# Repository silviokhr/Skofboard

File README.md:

# Split Ergonomic Wireless Gasket-Mounted Keyboard

<div align="center">
  
</div>

## Features

- **Ergonomic split design** — reduces wrist strain and promotes a more neutral typing position
- **Ortholinear layout**     — aligns keys in a grid, reducing finger travel distance with 3 dedicated thumb buttons
- **Gasket-mounted PCB**     — provides a dampened sound profile and soft keystroke feel
- **Magnetic closure**       — enables quick assembly and disassembly without tools
- **Reversible PCB design**  — single PCB works for both left and right halves
- **Hot-swappable switches** — easily swap or customize switches without soldering
- **ZMK firmware support**   — fully customizable keymap via ZMK Studio
- **Wireless connectivity**  — powered by the nice!nano v2.0 microcontroller

---

## Case

All case parts are CNC machined, and material selection significantly impacts the sound profile. The rigid aluminum base dampens resonance while the polycarbonate top provides acoustic transparency, and rounded internal surfaces minimize harsh reflections for a refined keystroke sound. STL files are included for 3D-printed case variants.

| Part | Material | Surface Finish |
|------|----------|----------------|
| Top casing | Polycarbonate (PC) | Blue-tinted vapor polishing |
| Bottom casing | Aluminum 6061 | Bead blasting + anodizing |

---

## Parts List (Bill of Materials)

Quantities are **per half** — a complete keyboard requires two of everything below.

| Qty | Component | Specification |
|-----|-----------|---------------|
| 8 | Corner magnet | Neodymium disc, ⌀4 × 3 mm |
| 16 | Edge magnet | Neodymium disc, ⌀2 × 3 mm |
| 6 | Large gasket foam | Poron, 4.5 × 7 × 2 mm |
| 2 | Small gasket foam | Poron, 4.5 × 4 × 2 mm |
| 4 | Rubber foot | ⌀8 × 1.6 mm |
| 1 | Microcontroller | nice!nano v2.0 |
| 2 | Microcontroller socket 12-pin | Mill Max 315-43-112-41-003000 |
| 24 | Socket pins | Mill Max 3320-0-00-15-00-00-03-0 |
| 1 | Battery | 3.7 V LiPo, 250 mAh, model 502030, 2P-PH connector |
| 1 | Battery connector | S2B-PH-K-S(LF)(SN) |
| 1 | Power switch | MSK12C02 (SMD slide switch) |
| 30 | Keyswitch | MX-format (any compatible switch) |
| 30 | Hotswap socket | Kailh MX-format |
| 30 | Diode | 1N4148W, SOD-123 |

### Part Notes

Only the parts below have constraints or behavior worth calling out; everything else fits as listed.

- **Magnets** — Cutouts are intentionally oversized to ensure a proper fit during assembly. Corner cutouts are ⌀4.1 mm × 3 mm deep; edge cutouts are ⌀2.1 mm × 3 mm deep.
- **Rubber feet** — Seat into ⌀8 mm × 1.5 mm-deep cutouts and must protrude a minimum of 0.1 mm below the case bottom for optimal grip.
- **Battery** — The cutout on the top plate is shared with the battery connector jack, which limits usable space. Optimal dimensions are **50 mm (H) × 20 mm (W) × 30 mm (D)**. ⚠️ Taller batteries are possible, but wider or longer batteries are not recommended and may not fit reliably.

---

## PCB Specifications

- **Layer count:** 2-layer
- **Material:** FR-4, 1.6 mm thickness
- **Copper weight:** 1 oz
- **Surface finish:** LeadFree HASL

**Design note:** The PCB switchplate (`SkofTopPlate.kicad_pcb`) is 1.6 mm FR-4 (standard manufacturing thickness), while standard MX switches are designed for 1.5 mm plates. Because of this 0.1 mm difference, switches fit securely but may feel slightly tight.

---

## Keymap

The default keymap is currently a placeholder and varies by region. To customize it, press the **`studio_unlock`** key on the left half — at **column 1, row 2** — to enter configuration mode in ZMK Studio.

---

## Assembly Guide

> Build is **per half** — repeat all steps for both. The PCB is reversible, so each half is configured by solder jumpers (step 3) before anything is populated.

**Case prep**

1. **Attach the feet** to the bottom casing.
2. **Glue in the magnets** (corner and edge) into their cutouts. ⚠️ Check polarity *before* gluing — all magnets must be oriented so the top and bottom casings attract when closed. (See Part Notes for fit.)

**PCB**

3. **Set the handedness** — close the solder-jumper bridges that configure the PCB for the left or right half (per the build files), **before** soldering any sockets:
   - **Microcontroller** jumpers — front (top) side
   - **Battery** jumpers — back (bottom) side
4. **Populate the PCB** — on the **back**, solder the diodes and hotswap sockets; on the **front**, solder the power switch, battery connector, and microcontroller sockets.
5. **Mount the nice!nano v2.0** — seat the header pins in the sockets, then mount the controller **face-down (component side against the PCB, bare back facing up)** and solder the pins so it stays removable.

**Power test** *(before switches — easier to fix solder issues now)*

6. **Connect the battery** with the power switch **off**, checking polarity.
7. **Flash and test** — flash the firmware (double-tap reset for the bootloader), power on, and confirm the half boots, pairs with the other half, and connects to your host.

**Plate + switches**

8. **Add the gasket foam** — place the foam strips in their positions per the build files.
9. **Install switches** — straighten any bent pins, fit 3–4 corner switches first to align the plate, then drop in the rest through the switchplate.

**Finish**

10. **Final check** — verify every key registers.
11. **Close the case** — join the top and bottom casings via the magnetic closure.

---

## Credits

This project uses open-source hardware footprints licensed under MIT and CC-BY-NC-SA 4.0 by Marco Massarelli (@ceoloide) and contributors.

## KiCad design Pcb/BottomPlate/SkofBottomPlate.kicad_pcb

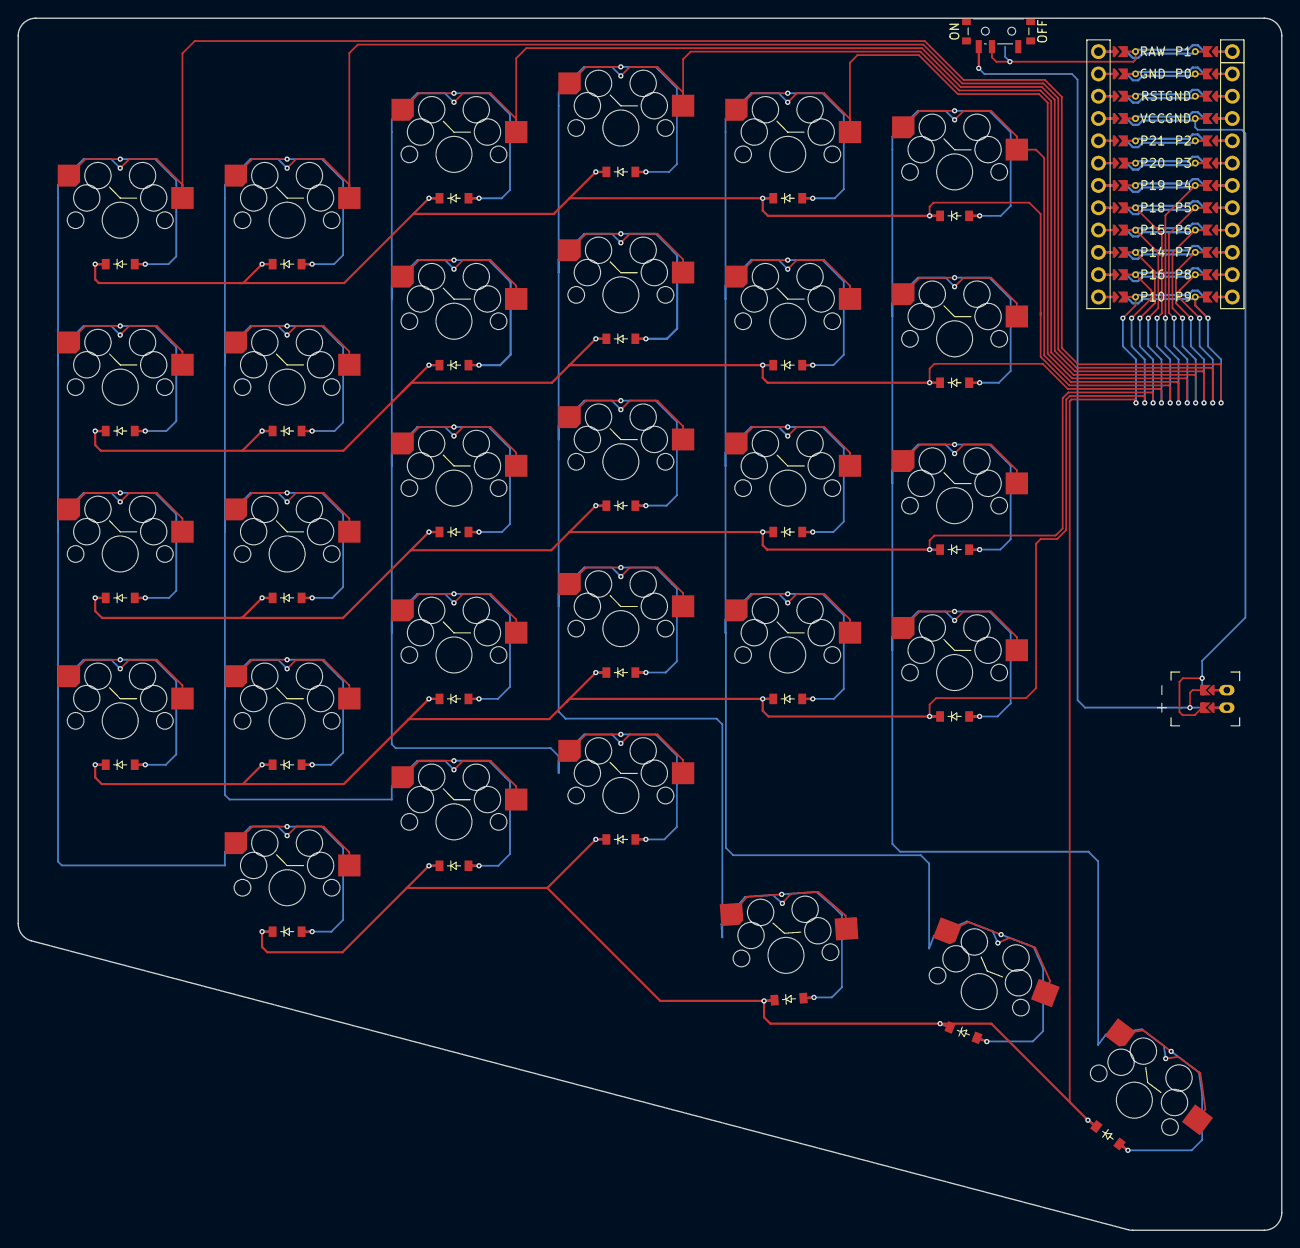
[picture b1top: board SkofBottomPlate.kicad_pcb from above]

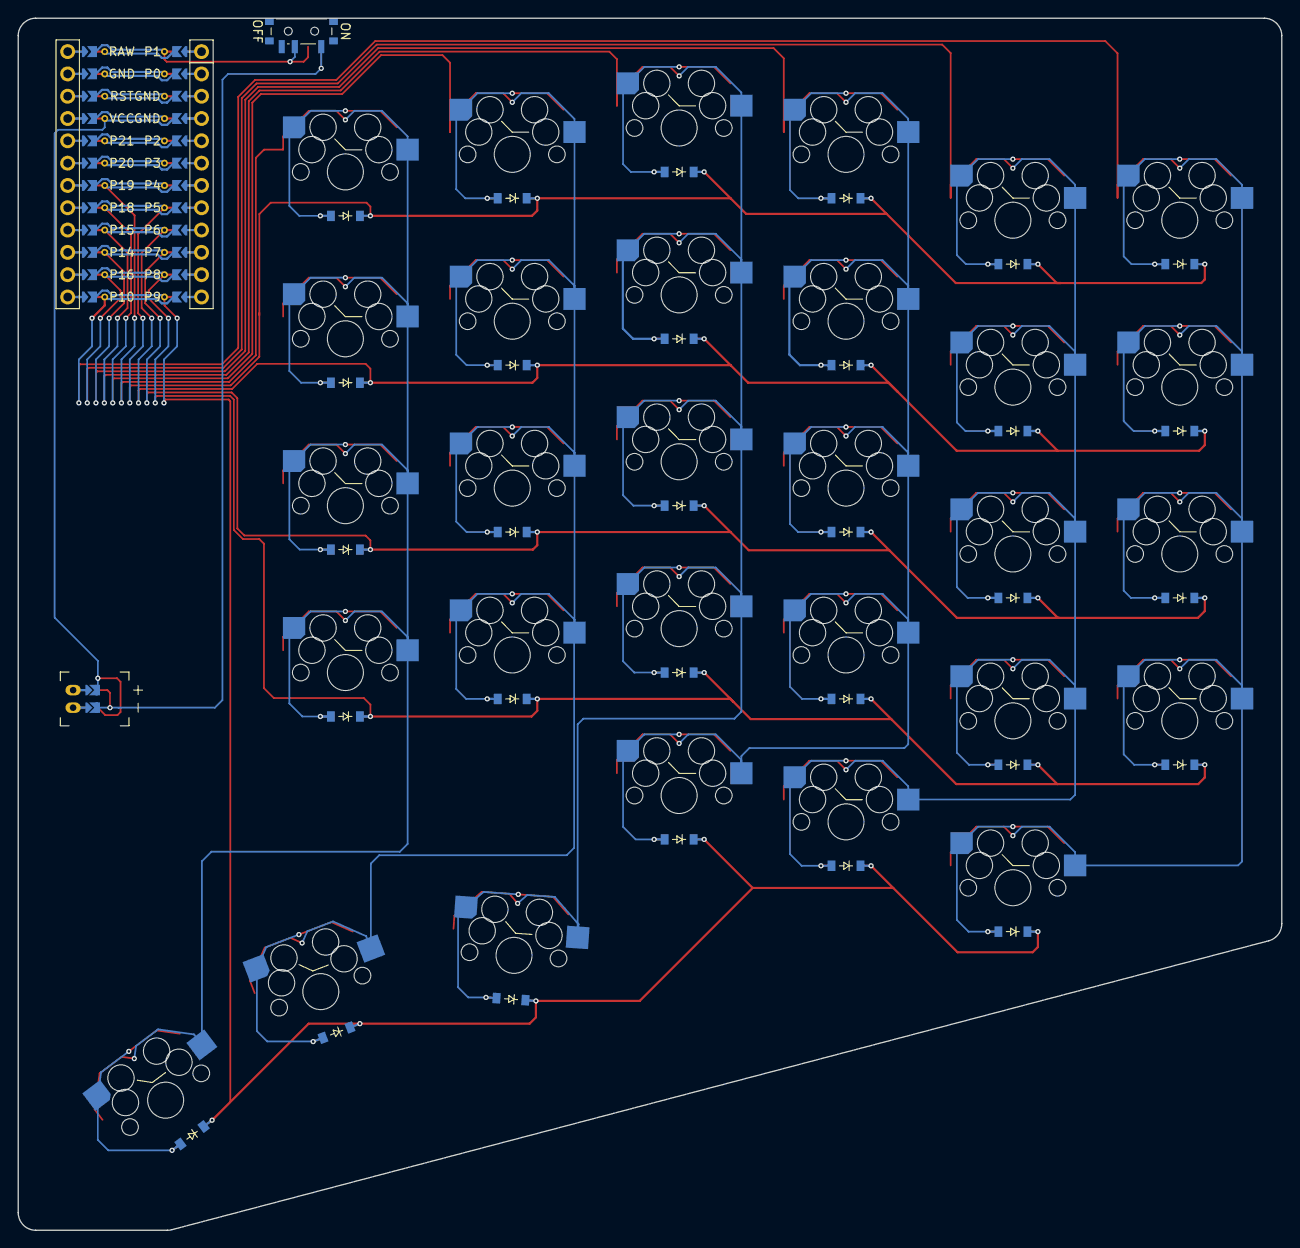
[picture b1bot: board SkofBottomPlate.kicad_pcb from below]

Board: 2 copper layers, 143.9 x 138.0 mm, 63 parts (30 on the bottom side), 46 nets.

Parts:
D1, D2, D3, D4, D5, D6, D7, D8, D9, D10, D11, D12, D13, D14, D15, D16, D17, D18, D19, D20, D21, D22, D23, D24, D25, D26, D27, D28, D29, D30: diode_tht_sod123
JST1: battery_connector_jst_ph_2
MCU1: mcu_nice_nano
PWR1: power_switch_smd_side
S1, S2, S3, S4, S5, S6, S7, S8, S9, S10, S11, S12, S13, S14, S15, S16, S17, S18, S19, S20, S21, S22, S23, S24, S25, S26, S27, S28, S29, S30: switch_mx

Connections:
BAT_P: JST1.1, PWR1.1, PWR1.3
GND: JST1.2, MCU1.103, MCU1.104, MCU1.123
JST1_1: JST1.11, JST1.21, JST1.31
JST1_2: JST1.12, JST1.22, JST1.32
P4: MCU1.107, S24.1, S25.1, S26.1, S27.1, S30.1
P5: MCU1.108, S20.1, S21.1, S22.1, S23.1, S29.1
P6: MCU1.109, S16.1, S17.1, S18.1, S19.1, S28.1
P7: MCU1.110, S11.1, S12.1, S13.1, S14.1, S15.1
P8: MCU1.111, S6.1, S7.1, S8.1, S9.1, S10.1
P9: MCU1.112, S1.1, S2.1, S3.1, S4.1, S5.1
P10: D5.1, D10.1, D15.1, D28.1, D29.1, D30.1, MCU1.113
P14: D2.1, D7.1, D12.1, D17.1, D21.1, D25.1, MCU1.115
P15: D3.1, D8.1, D13.1, D18.1, D22.1, D26.1, MCU1.116
P16: D1.1, D6.1, D11.1, D16.1, D20.1, D24.1, MCU1.114
P18: D4.1, D9.1, D14.1, D19.1, D23.1, D27.1, MCU1.117
RAW: MCU1.124, PWR1.2
filler_cluster: D28.2, S28.2
index_home: D20.2, S20.2
index_num: D22.2, S22.2
index_nums: D23.2, S23.2
index_top: D21.2, S21.2
inner_home: D24.2, S24.2
inner_num: D26.2, S26.2
inner_nums: D27.2, S27.2
inner_top: D25.2, S25.2
layer_cluster: D29.2, S29.2
middle_bottom: D15.2, S15.2
middle_home: D16.2, S16.2
middle_num: D18.2, S18.2
middle_nums: D19.2, S19.2
middle_top: D17.2, S17.2
outer_home: D1.2, S1.2
outer_num: D3.2, S3.2
outer_nums: D4.2, S4.2
outer_top: D2.2, S2.2
pinky_bottom: D5.2, S5.2
pinky_home: D6.2, S6.2
pinky_num: D8.2, S8.2
pinky_nums: D9.2, S9.2
pinky_top: D7.2, S7.2
ring_bottom: D10.2, S10.2
ring_home: D11.2, S11.2
ring_num: D13.2, S13.2
ring_nums: D14.2, S14.2
ring_top: D12.2, S12.2
space_cluster: D30.2, S30.2

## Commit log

2026-06-11 build.yaml fix
2026-06-11 README initial
2026-06-15 readme format update
2026-06-15 readme overhaul
2026-06-16 readme and image update
2026-06-16 rendering issue fix
2026-06-19 improved zmk studio layout
